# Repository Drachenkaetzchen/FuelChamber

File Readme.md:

# FuelChamber Toolhead PCB

This is a drop-in remix of [hartk's Afterburner Toolhead PCB](https://github.com/hartk1213/Voron-Hardware/tree/master/Afterburner_Toolhead_PCB) v3.1 with the following changes:

- On-board 12V regulator to allow the operation of 12V fans, selectable for each fan using solder jumpers. Maximum 1A for the 12V rail.
- Pin Compatible with the Afterburner Toolhead PCB
- Decreased height to avoid interference with the Voron 1.8 gantry
- Increased clearance for the mounting screws to avoid damaging the traces

Rev A and Rev B have no support for the BAT85 Diode!

# Usage

This PCB replaces a hartk Afterburner Toolhead PCB. Replace your 24V fans with 12V fans as needed, and use
the solder jumpers to configure the voltage. Simply remove the old PCB and insert this one.

For assembly: Always start with the lowest height components and work your way up.

Note this PCB is `experimental` because it has yet to be determined if the DC/DC converters survive the
constant toolhead movements. Although the VR10S12 did survive for 100 printing hours now, it's unlikely that they fail, but we never know until we try.s

# BOM

## Warning: Outdated!

| Designator           | Footprint       | Value            | Remarks
|----------------------|-----------------|------------------|--------------
| C1                   | 1206            | 10µF 35V         | ceramic caps are okay, too
| CT                   | 0805            | CMFB103F3950FANT | 10kΩ ±1% 3950K NTC Thermistor
| D1 (for VR10S12 )    | SMB             | 22µF 16V         | use a 1206 capacitor, 10µF ceramic is often okay, too
| D1 (for R-78C12-1.0) | SMB             | 1SMB5928BT3G     | as specified by the R-78C12-1.0 datasheet
| DC1                  | SIP 3           | VR10S12          | The original design used a Recom R-78C12-1.0, but a XP Power VR10S12 is cheaper
| LED1                 | 0805            | LED 0805         | Use any 0805 chip LED, indicates heater activity
| R1                   | 0805            | see remarks      | Calculate this appropriately for LED1 and 24V!
| HE0, HEF, PCF, XES   | JST-XH-02       | 2-pin JST XH     |
| ABL                  | JST-XH-03       | 3-pin JST XH     |
| E-STEP               | JST-XH-04       | 4-pin JST XH     |
| HE0                  | MOLEX 436500200 | MOLEX 436500200  |
| -                    | MOLEX 430451400 | MOLEX 430451400  |		

# Alternative Voltage Regulators

You can use one of these DC/DC voltage regulators if you are having trouble finding the `VR10S12`. Please refer
to the datasheet for any input/output decoupling.

__Please do not use any linear voltage regulators, because these require a heatsink and the acceleration forces will most likely shear off the voltage regulator over time.__

## 1A DC/DC Converters

- Traco Power `TSR 1-24120`
- Recom `R-78C12-1.0`

## 500mA DC/DC Converters

Use these only if you are sure that your fans will not exceed the current capability! The peak current when
the fans are starting up can be higher than specified!

- Aimtec `AMSR-7812-NZ`
- Traco Power `TSR 0.5-24120`
- XP Power `SR05S12`
 
# Design Notes

- The trace widths are calculated to allow operation within a 70°C chamber and a maximum temperature
  rise of 10°C.
- The pin assignments of the 14 pin MicroFit3 connector is unchanged
- The original version used a Recom R-78C12-1.0, but has been changed to a VR10S12 which lowers the cost significantly
- I've been using the Rev.A with a VR10S12 for about 100 hours of printing in conjunction with a single 12V fan, no issues observed so far

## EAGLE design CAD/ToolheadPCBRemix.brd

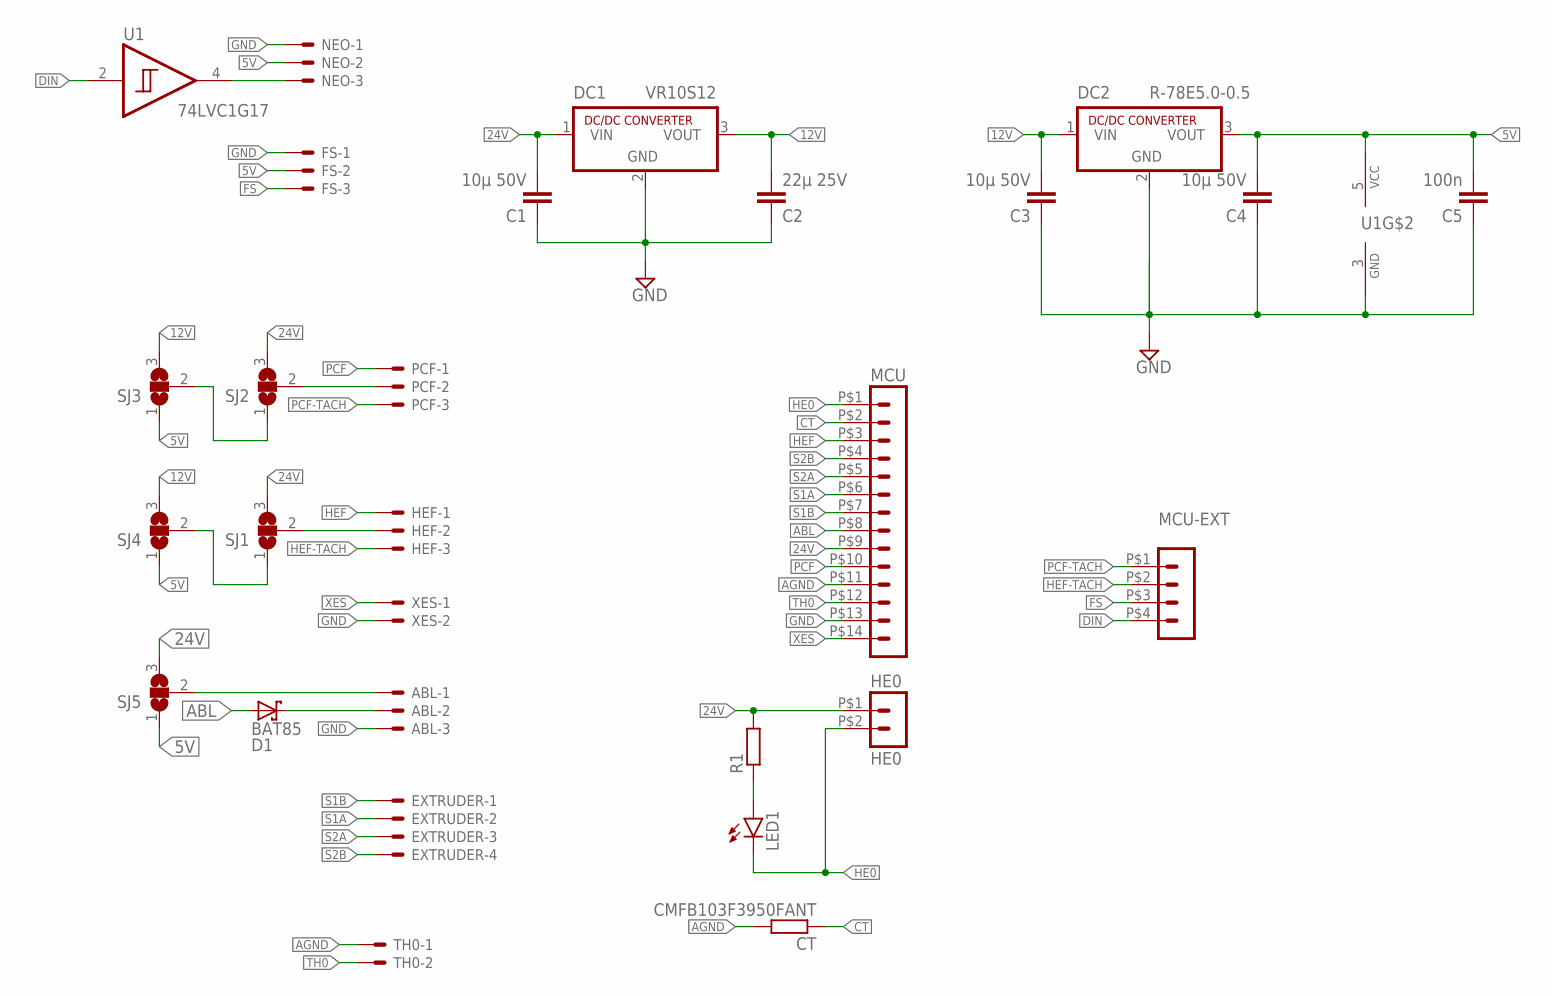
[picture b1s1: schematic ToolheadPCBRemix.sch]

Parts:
ABL: JST-XH-03-PIN-ROUND-PAD; JST-XH-03-PACKAGE-ROUND-PAD
C1, C3, C4: 10µ 50V; C1206
C2: 22µ 25V; C1206
C5: 100n; C0805
CT: CMFB103F3950FANT; R0805
D1: BAT85; SOD68
DC1: VR10S12; SIP3
DC2: R-78E5.0-0.5; SIP3
EXTRUDER: JST-XH-04-PIN-ROUND-PAD; JST-XH-04-PACKAGE-ROUND-PAD
FS: JST-XH-03-PIN-ROUND-PAD; JST-XH-03-PACKAGE-ROUND-PAD
HE0: HE0; 43650-0200
HEF: JST-XH-03-PIN-ROUND-PAD; JST-XH-03-PACKAGE-ROUND-PAD
LED1: LEDCHIPLED_0805; CHIPLED_0805
MCU: HEADER_POS14_43045-1400; 43045-1400
MCU-EXT: HEADER_POS4_43045-0401; 43045-0400
NEO: JST-XH-03-PIN-ROUND-PAD; JST-XH-03-PACKAGE-ROUND-PAD
PCF: JST-XH-03-PIN-ROUND-PAD; JST-XH-03-PACKAGE-ROUND-PAD
R1: R-EU_R0805; R0805
SJ1, SJ2, SJ3, SJ4, SJ5: SJ2W; SJ_2
TH0: JST-XH-02-PIN-ROUND-PAD; JST-XH-02-PACKAGE-ROUND-PAD
U1: 74LVC1G17; SOT23-5
XES: JST-XH-02-PIN-ROUND-PAD; JST-XH-02-PACKAGE-ROUND-PAD

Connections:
5V: C4.2, C5.2, DC2.3 (VOUT), FS.2, NEO.2, SJ3.1, SJ4.1, SJ5.1, U1.5 (VCC)
12V: C2.2, C3.2, DC1.3 (VOUT), DC2.1 (VIN), SJ3.3, SJ4.3
24V: C1.2, DC1.1 (VIN), HE0.P$1 (1), MCU.P$9 (9), R1.2, SJ1.3, SJ2.3, SJ5.3
ABL: D1.A, MCU.P$8 (8)
AGND: CT.2, MCU.P$11 (11), TH0.1
CT: CT.1, MCU.P$2 (2)
DIN: MCU-EXT.P$4 (4), U1.2 (A)
FS: FS.3, MCU-EXT.P$3 (3)
GND: ABL.3, C1.1, C2.1, C3.1, C4.1, C5.1, DC1.2 (GND), DC2.2 (GND), FS.1, MCU.P$13 (13), NEO.1, U1.3 (GND), XES.2
HE0: HE0.P$2 (2), LED1.C, MCU.P$1 (1)
HEF: HEF.1, MCU.P$3 (3)
HEF-TACH: HEF.3, MCU-EXT.P$2 (2)
unnamed: LED1.A, R1.1
unnamed: PCF.2, SJ2.2
unnamed: HEF.2, SJ1.2
unnamed: NEO.3, U1.4 (Y)
unnamed: SJ2.1, SJ3.2
unnamed: SJ1.1, SJ4.2
unnamed: ABL.1, SJ5.2
unnamed: ABL.2, D1.C (K)
PCF: MCU.P$10 (10), PCF.1
PCF-TACH: MCU-EXT.P$1 (1), PCF.3
S1A: EXTRUDER.2, MCU.P$6 (6)
S1B: EXTRUDER.1, MCU.P$7 (7)
S2A: EXTRUDER.3, MCU.P$5 (5)
S2B: EXTRUDER.4, MCU.P$4 (4)
TH0: MCU.P$12 (12), TH0.2
XES: MCU.P$14 (14), XES.1

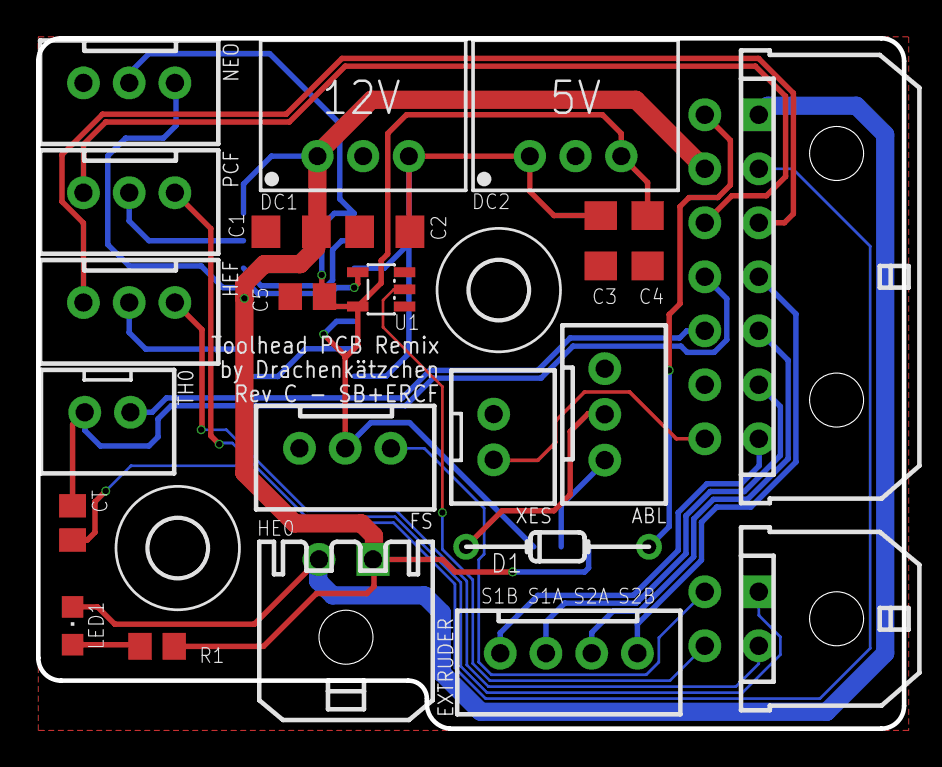
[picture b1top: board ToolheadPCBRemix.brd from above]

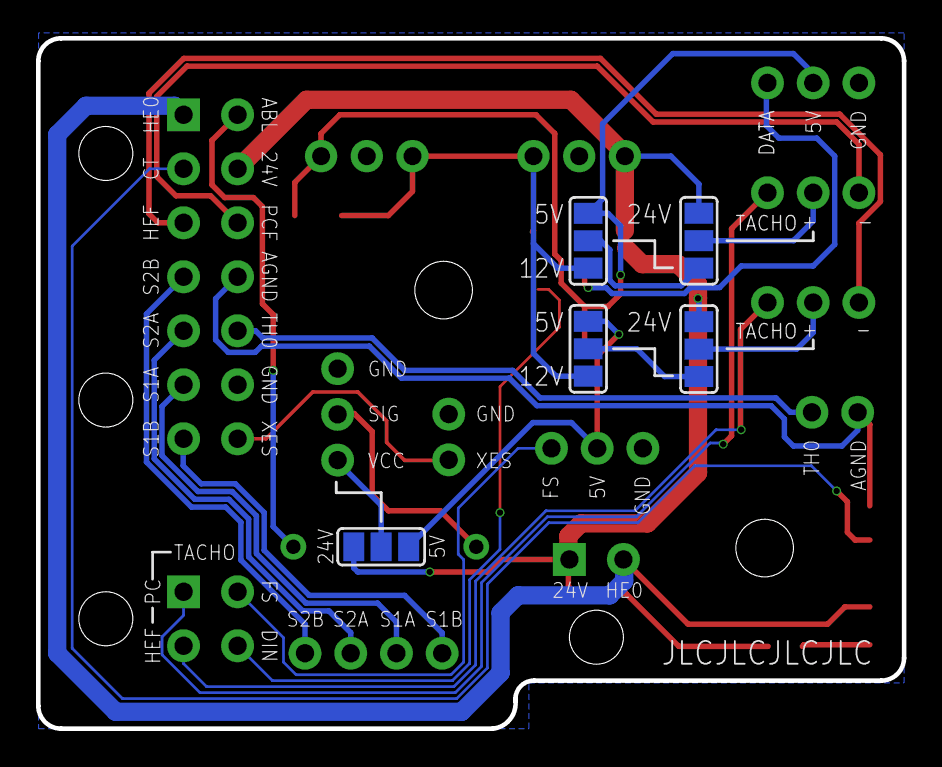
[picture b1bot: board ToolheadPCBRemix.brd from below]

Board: 2 copper layers, 48.1 x 38.4 mm, 30 parts (5 on the bottom side), 28 nets.

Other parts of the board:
E$1, E$2: 3,2

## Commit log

2021-11-05 Included photo, remarks about replacements for the DC-DC converter
2021-11-06 This project is now called FuelChamber
2022-10-02 Update to dual vregs (12V/5V)
2022-10-02 Fixed PCB imge path
